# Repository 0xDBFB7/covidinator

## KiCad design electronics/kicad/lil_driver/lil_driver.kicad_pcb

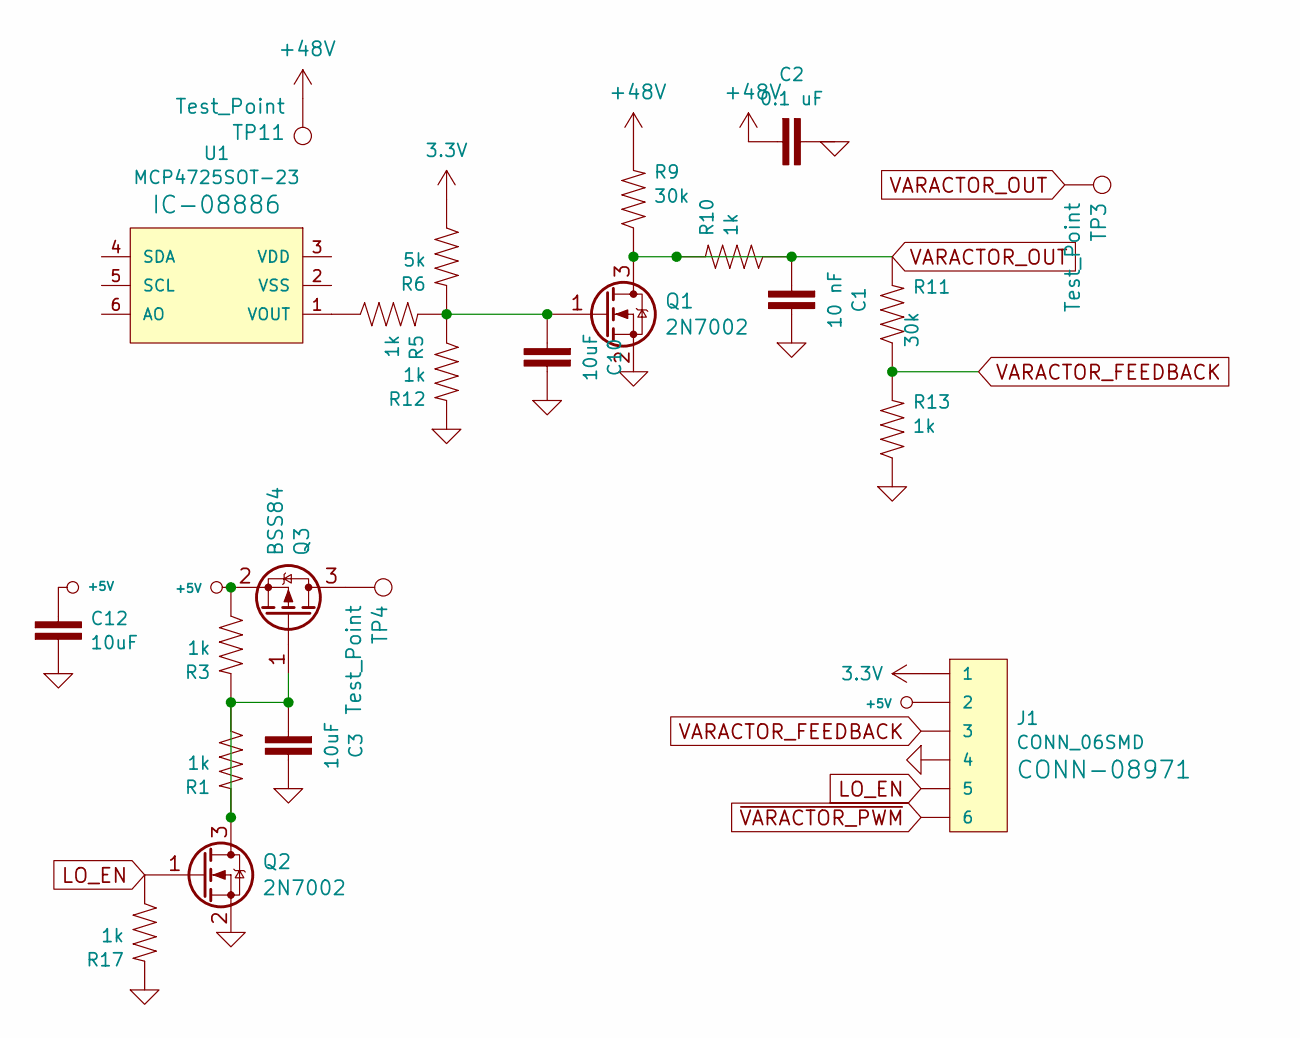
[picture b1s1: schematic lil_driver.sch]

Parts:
C1: 10 nF; 0603
C2: 0.1 uF; 0603
C3, C10: 10uF; 0603
C12: 10uF; 1206
J1: CONN_06SMD; 1X06-SMD_RA_MALE
Q1, Q2: 2N7002; SOT-23
Q3: BSS84; SOT-23
R1, R3, R5, R10, R12, R13, R17: 1k; R_0603_1608Metric
R6: 5k; R_0603_1608Metric
R9, R11: 30k; R_0603_1608Metric
TP3, TP4: Test_Point; TestPoint_Pad_2.0x2.0mm
TP11: Test_Point; TestPoint_Pad_1.5x1.5mm
U1: MCP4725SOT-23; SOT23-6

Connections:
3.3V: J1.1, R6.1
+5V: C12.1, J1.2, Q3.2 (S), R3.1
+48V: C2.2, R9.2, TP11.1
GND: C1.1, C2.1, C3.1, C10.1, C12.2, J1.4, Q1.2 (S), Q2.2 (S), R12.2, R13.1, R17.2
LO_EN: J1.5, Q2.1 (G), R17.1
unnamed: C3.2, Q2.3 (D), Q3.1 (G), R1.1, R1.2, R3.2
unnamed: C10.2, Q1.1 (G), R5.2, R6.2, R12.1
unnamed: Q3.3 (D), TP4.1
unnamed: R5.1, U1.1 (VOUT)
VARACTOR_FEEDBACK: J1.3, R11.1, R13.2
VARACTOR_OUT: C1.2, Q1.3 (D), R9.1, R10.1, R10.2, R11.2, TP3.1
~VARACTOR_PWM: J1.6

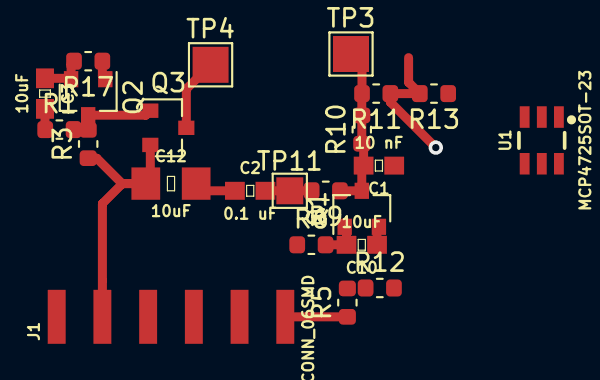
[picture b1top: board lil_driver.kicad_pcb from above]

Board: 2 copper layers, 23 parts (0 on the bottom side), 11 nets.

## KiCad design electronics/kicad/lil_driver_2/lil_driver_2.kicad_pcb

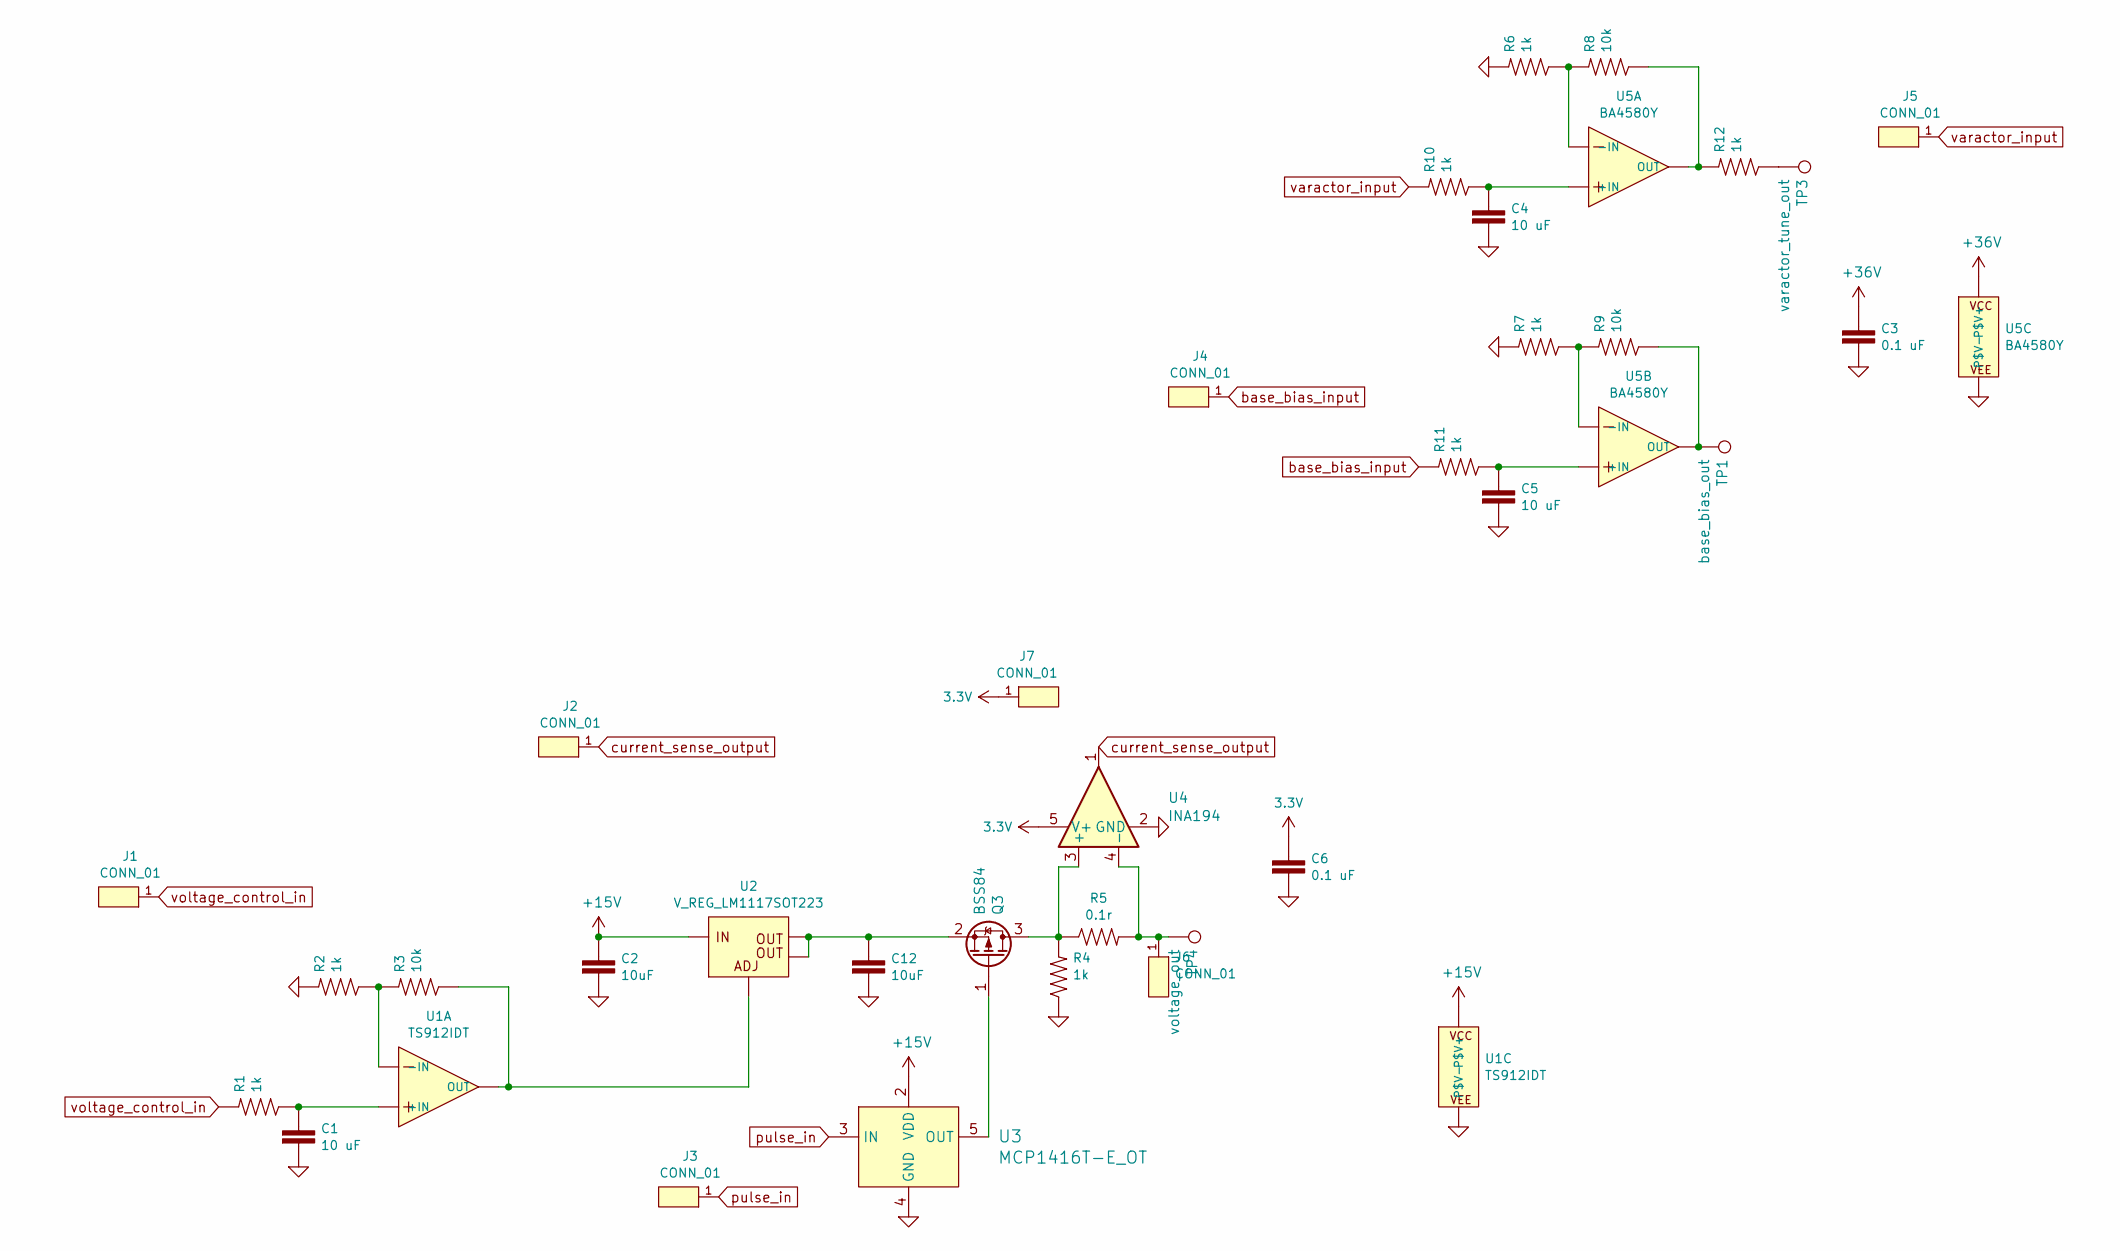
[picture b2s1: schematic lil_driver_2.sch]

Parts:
C1, C4, C5: 10 uF; 0603
C2, C12: 10uF; 1206
C3, C6: 0.1 uF; 0603
J1, J2, J3, J4, J5, J6, J7: CONN_01; 1X01
Q3: BSS84; SOT-23
R1, R2, R4, R6, R7, R10, R11, R12: 1k; R_0603_1608Metric
R3, R8, R9: 10k; R_0603_1608Metric
R5: 0.1r; 0805
TP1: base_bias_out; TestPoint_Pad_2.0x2.0mm
TP3: varactor_tune_out; TestPoint_Pad_2.0x2.0mm
TP4: voltage_out; TestPoint_Pad_2.0x2.0mm
U1: TS912IDT; SOIC-8_3.9x4.9mm_P1.27mm
U2: V_REG_LM1117SOT223; SOT223
U3: MCP1416T-E_OT; SOT-753; MPN MCP1416T-E/OT; Digi-Key_PN MCP1416T-E/OTCT-ND
U4: INA194; SOT-23-5
U5: BA4580Y; SOIC-8_3.9x4.9mm_P1.27mm

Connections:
3.3V: C6.1, J7.1, U4.5 (V+)
+15V: C2.1, U1.8 (P$V+), U2.3 (IN), U3.2 (VDD)
+36V: C3.1, U5.8 (P$V+)
GND: C1.2, C2.2, C3.2, C4.2, C5.2, C6.2, C12.2, R2.2, R4.1, R6.2, R7.2, U1.4 (P$V-), U3.4 (GND), U4.2 (GND), U5.4 (P$V-)
unnamed: C1.1, R1.1, U1.3 (+IN)
unnamed: C4.1, R10.1, U5.3 (+IN)
unnamed: C5.1, R11.1, U5.5 (+IN)
unnamed: C12.1, Q3.2 (S), U2.2 (OUT), U2.4 (OUT)
unnamed: J6.1, R5.2, TP4.1, U4.4 (-)
unnamed: Q3.1 (G), U3.5 (OUT)
unnamed: Q3.3 (D), R4.2, R5.1, U4.3 (+)
unnamed: R2.1, R3.2, U1.2 (-IN)
unnamed: R3.1, U1.1 (OUT), U2.1 (ADJ)
unnamed: R6.1, R8.2, U5.2 (-IN)
unnamed: R7.1, R9.2, U5.6 (-IN)
unnamed: R9.1, TP1.1, U5.7 (OUT)
unnamed: R12.1, TP3.1
unnamed: R8.1, R12.2, U5.1 (OUT)
base_bias_input: J4.1, R11.2
current_sense_output: J2.1, U4.1
pulse_in: J3.1, U3.3 (IN)
varactor_input: J5.1, R10.2
voltage_control_in: J1.1, R1.2

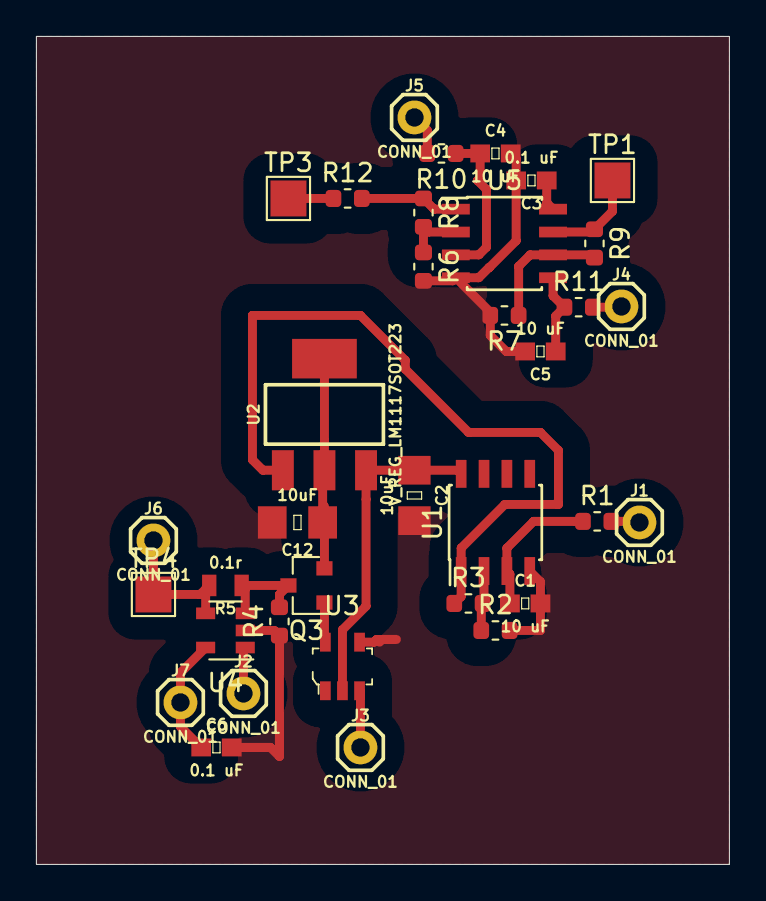
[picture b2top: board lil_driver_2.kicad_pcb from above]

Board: 2 copper layers, 38.5 x 46.0 mm, 35 parts (0 on the bottom side), 23 nets.

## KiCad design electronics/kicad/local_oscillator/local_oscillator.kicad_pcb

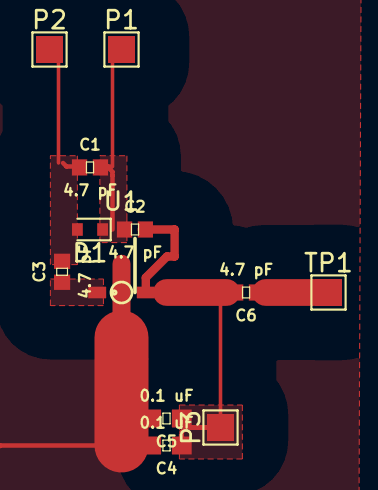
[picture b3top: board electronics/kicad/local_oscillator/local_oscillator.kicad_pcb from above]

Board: 2 copper layers, 12 parts (0 on the bottom side), 5 nets.

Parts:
C1, C2, C3, C6: 4.7 pF; 0402
C4, C5: 0.1 uF; 0603
D1: D; D_SOD-523
P1, P2, P3: TestPoint:TestPoint_Pad_1.5x1.5mm; TestPoint_Pad_1.5x1.5mm
TP1: SMA; TestPoint_Pad_1.5x1.5mm
U1: CE3520K3; 4-Micro-X

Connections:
/GATE: C3.1, U1.4
/VCC: C2.2, C4.1, C5.1, C6.2, P3.1, U1.2
/VCO1: C1.1, C3.2, D1.2, P2.1
/VCO2: C1.2, C2.1, D1.1, P1.1
GND: C4.2, C5.2, U1.1, U1.3

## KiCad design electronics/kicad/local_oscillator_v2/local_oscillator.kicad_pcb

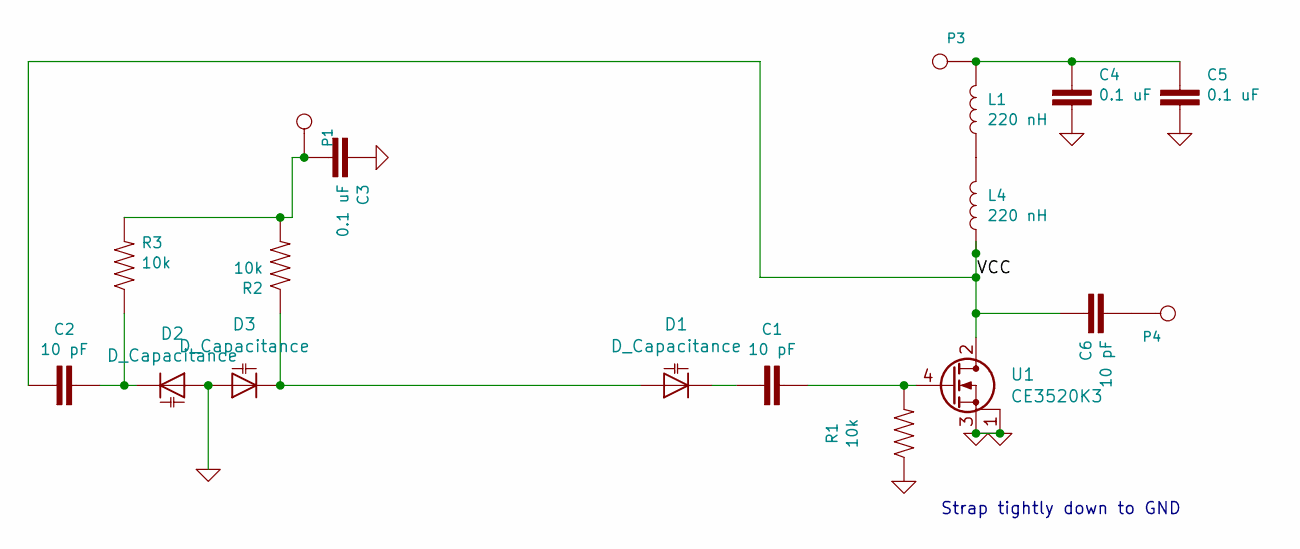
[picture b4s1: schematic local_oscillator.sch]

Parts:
C1, C2, C6: 10 pF; 0402
C3, C4, C5: 0.1 uF; 0603
D1, D2, D3: D_Capacitance; D_SOD-523
L1, L4: 220 nH; 0402
P1: T; TestPoint_Pad_1.5x1.5mm
P3, P4: a; TestPoint_Pad_1.5x1.5mm
R1, R2, R3: 10k; 0402
U1: CE3520K3; 4-Micro-X

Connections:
/VCC: C2.2, C6.2, L4.1, U1.2
GND: C3.1, C4.2, C5.2, D2.2 (A), D3.2 (A), R1.1, U1.1, U1.3
unnamed: C1.1, R1.2, U1.4
unnamed: C1.2, D1.1 (K)
unnamed: C2.1, D2.1 (K), R3.1
unnamed: C3.2, P1.1, R2.2, R3.2
unnamed: C4.1, C5.1, L1.2, P3.1
unnamed: C6.1, P4.1
unnamed: D1.2 (A), D3.1 (K), R2.1
unnamed: L1.1, L4.2

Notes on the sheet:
Strap tightly down to GND

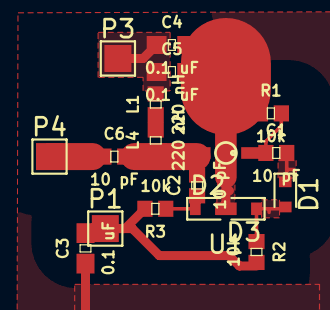
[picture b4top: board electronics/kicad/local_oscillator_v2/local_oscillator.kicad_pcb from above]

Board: 2 copper layers, 18 parts (0 on the bottom side), 10 nets.

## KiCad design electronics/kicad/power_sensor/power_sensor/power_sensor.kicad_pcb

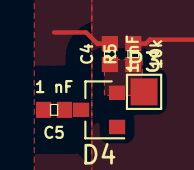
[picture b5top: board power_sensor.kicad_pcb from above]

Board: 2 copper layers, 5 parts (0 on the bottom side), 3 nets.

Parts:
C4, C5: 1 nF; 0402
D4: BAT15-04; SOT-23
P3: a; TestPoint_Pad_1.5x1.5mm
R5: 10k; 0402

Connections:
GND: C4.2, R5.2
unnamed: C4.1, D4.2, P3.1, R5.1
unnamed: C5.1, D4.3

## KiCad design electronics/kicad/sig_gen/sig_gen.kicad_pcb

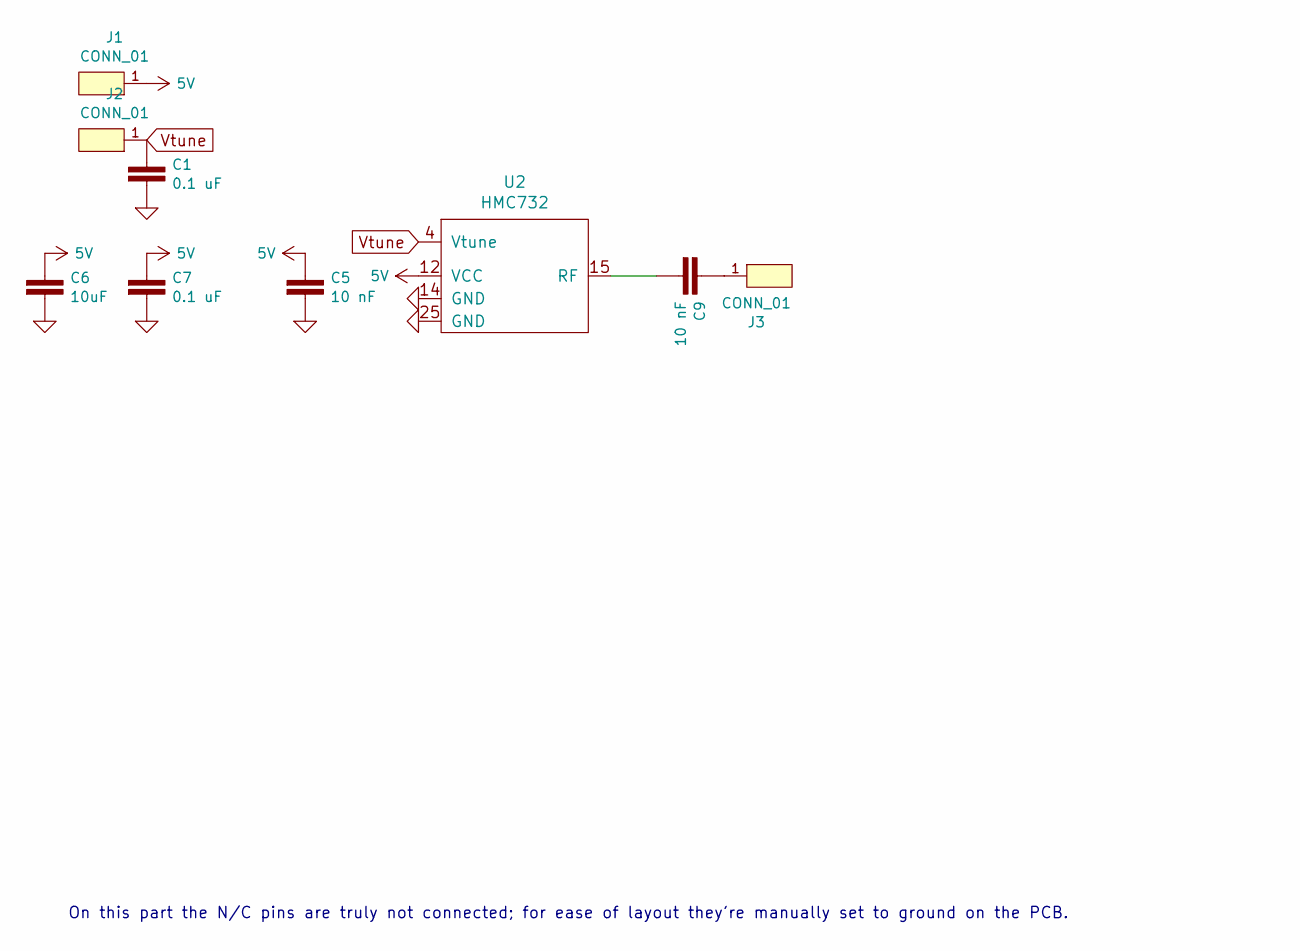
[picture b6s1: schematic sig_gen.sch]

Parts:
C1, C7: 0.1 uF; 0603
C5: 10 nF; C_0402_1005Metric
C6: 10uF; 1206
C9: 10 nF; 0402
J1, J2, J3: CONN_01; TestPoint_Pad_1.5x1.5mm
U2: HMC732; QFN-24-1EP_4x4mm_P0.5mm_EP2.6x2.6mm

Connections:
5V: C5.1, C6.1, C7.1, J1.1, U2.12 (VCC)
GND: C1.2, C5.2, C6.2, C7.2, U2.14 (GND), U2.25 (GND)
unnamed: C9.1, J3.1
unnamed: C9.2, U2.15 (RF)
Vtune: C1.1, J2.1, U2.4 (Vtune)

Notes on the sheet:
On this part the N/C pins are truly not connected; for ease of layout they're manually set to ground on the PCB.

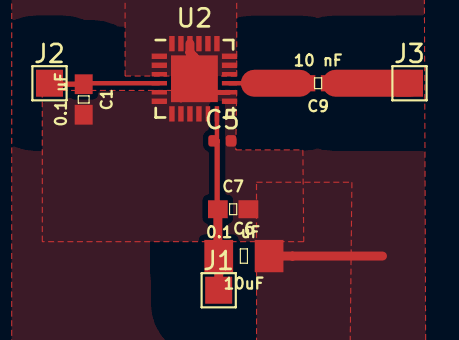
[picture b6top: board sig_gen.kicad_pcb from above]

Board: 2 copper layers, 9 parts (0 on the bottom side), 5 nets.

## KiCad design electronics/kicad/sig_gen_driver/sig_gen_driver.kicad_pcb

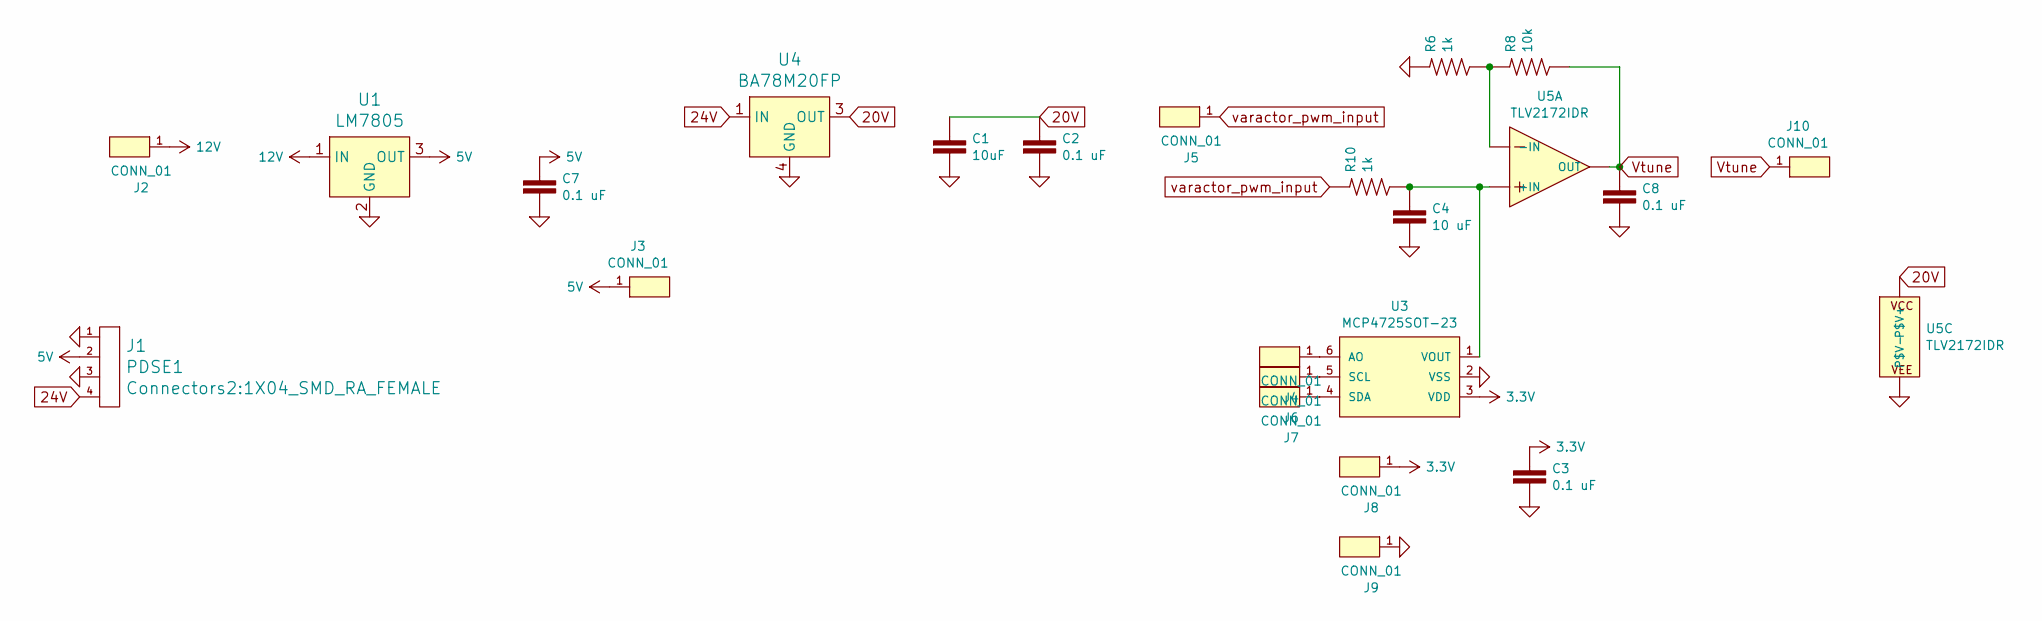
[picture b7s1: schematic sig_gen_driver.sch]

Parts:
C1: 10uF; 1206
C2, C3, C7, C8: 0.1 uF; 0603
C4: 10 uF; 0603
J1: PDSE1; 1X04_SMD_RA_FEMALE
J2, J4, J5, J6, J7, J8, J9: CONN_01; 1X01
J3, J10: CONN_01; TestPoint_Pad_1.5x1.5mm
R6, R10: 1k; R_0603_1608Metric
R8: 10k; R_0603_1608Metric
U1: LM7805; SOT-223; MPN LM7812CT; Digi-Key_PN LM7812CTFS-ND
U3: MCP4725SOT-23; SOT23-6
U4: BA78M20FP; TO-252-3; MPN MC7805BDTRKG; Digi-Key_PN MC7805BDTRKGOSCT-ND
U5: TLV2172IDR; SOIC-8_3.9x4.9mm_P1.27mm

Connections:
3.3V: C3.1, J8.1, U3.3 (VDD)
5V: C7.1, J1.2, J3.1, U1.3 (OUT)
12V: J2.1, U1.1 (IN)
20V: C1.1, C2.1, U4.3 (OUT), U5.8 (P$V+)
24V: J1.4, U4.1 (IN)
GND: C1.2, C2.2, C3.2, C4.2, C7.2, C8.2, J1.1, J1.3, J9.1, R6.2, U1.2 (GND), U3.2 (VSS), U4.4 (GND), U5.4 (P$V-)
unnamed: C4.1, R10.1, U3.1 (VOUT), U5.3 (+IN)
unnamed: J4.1, U3.6 (AO)
unnamed: J6.1, U3.5 (SCL)
unnamed: J7.1, U3.4 (SDA)
unnamed: R6.1, R8.2, U5.2 (-IN)
Vtune: C8.1, J10.1, R8.1, U5.1 (OUT)
varactor_pwm_input: J5.1, R10.2

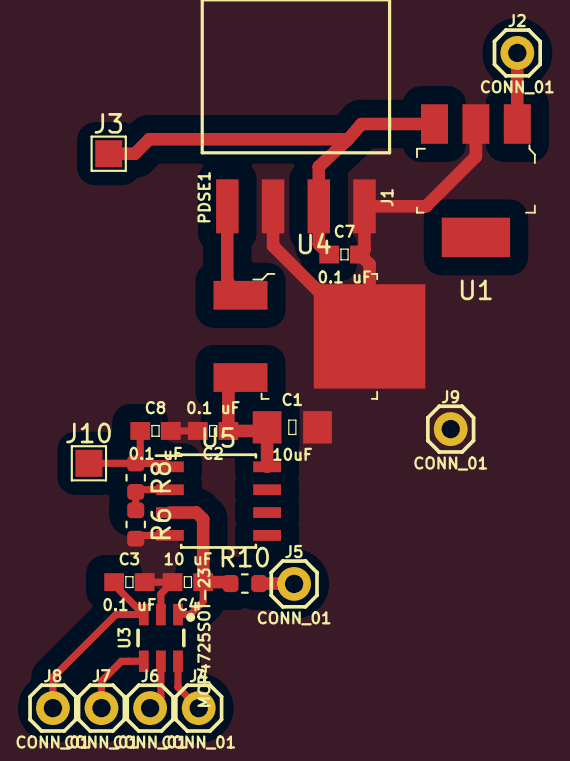
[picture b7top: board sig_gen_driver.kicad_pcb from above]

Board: 2 copper layers, 23 parts (0 on the bottom side), 13 nets.
